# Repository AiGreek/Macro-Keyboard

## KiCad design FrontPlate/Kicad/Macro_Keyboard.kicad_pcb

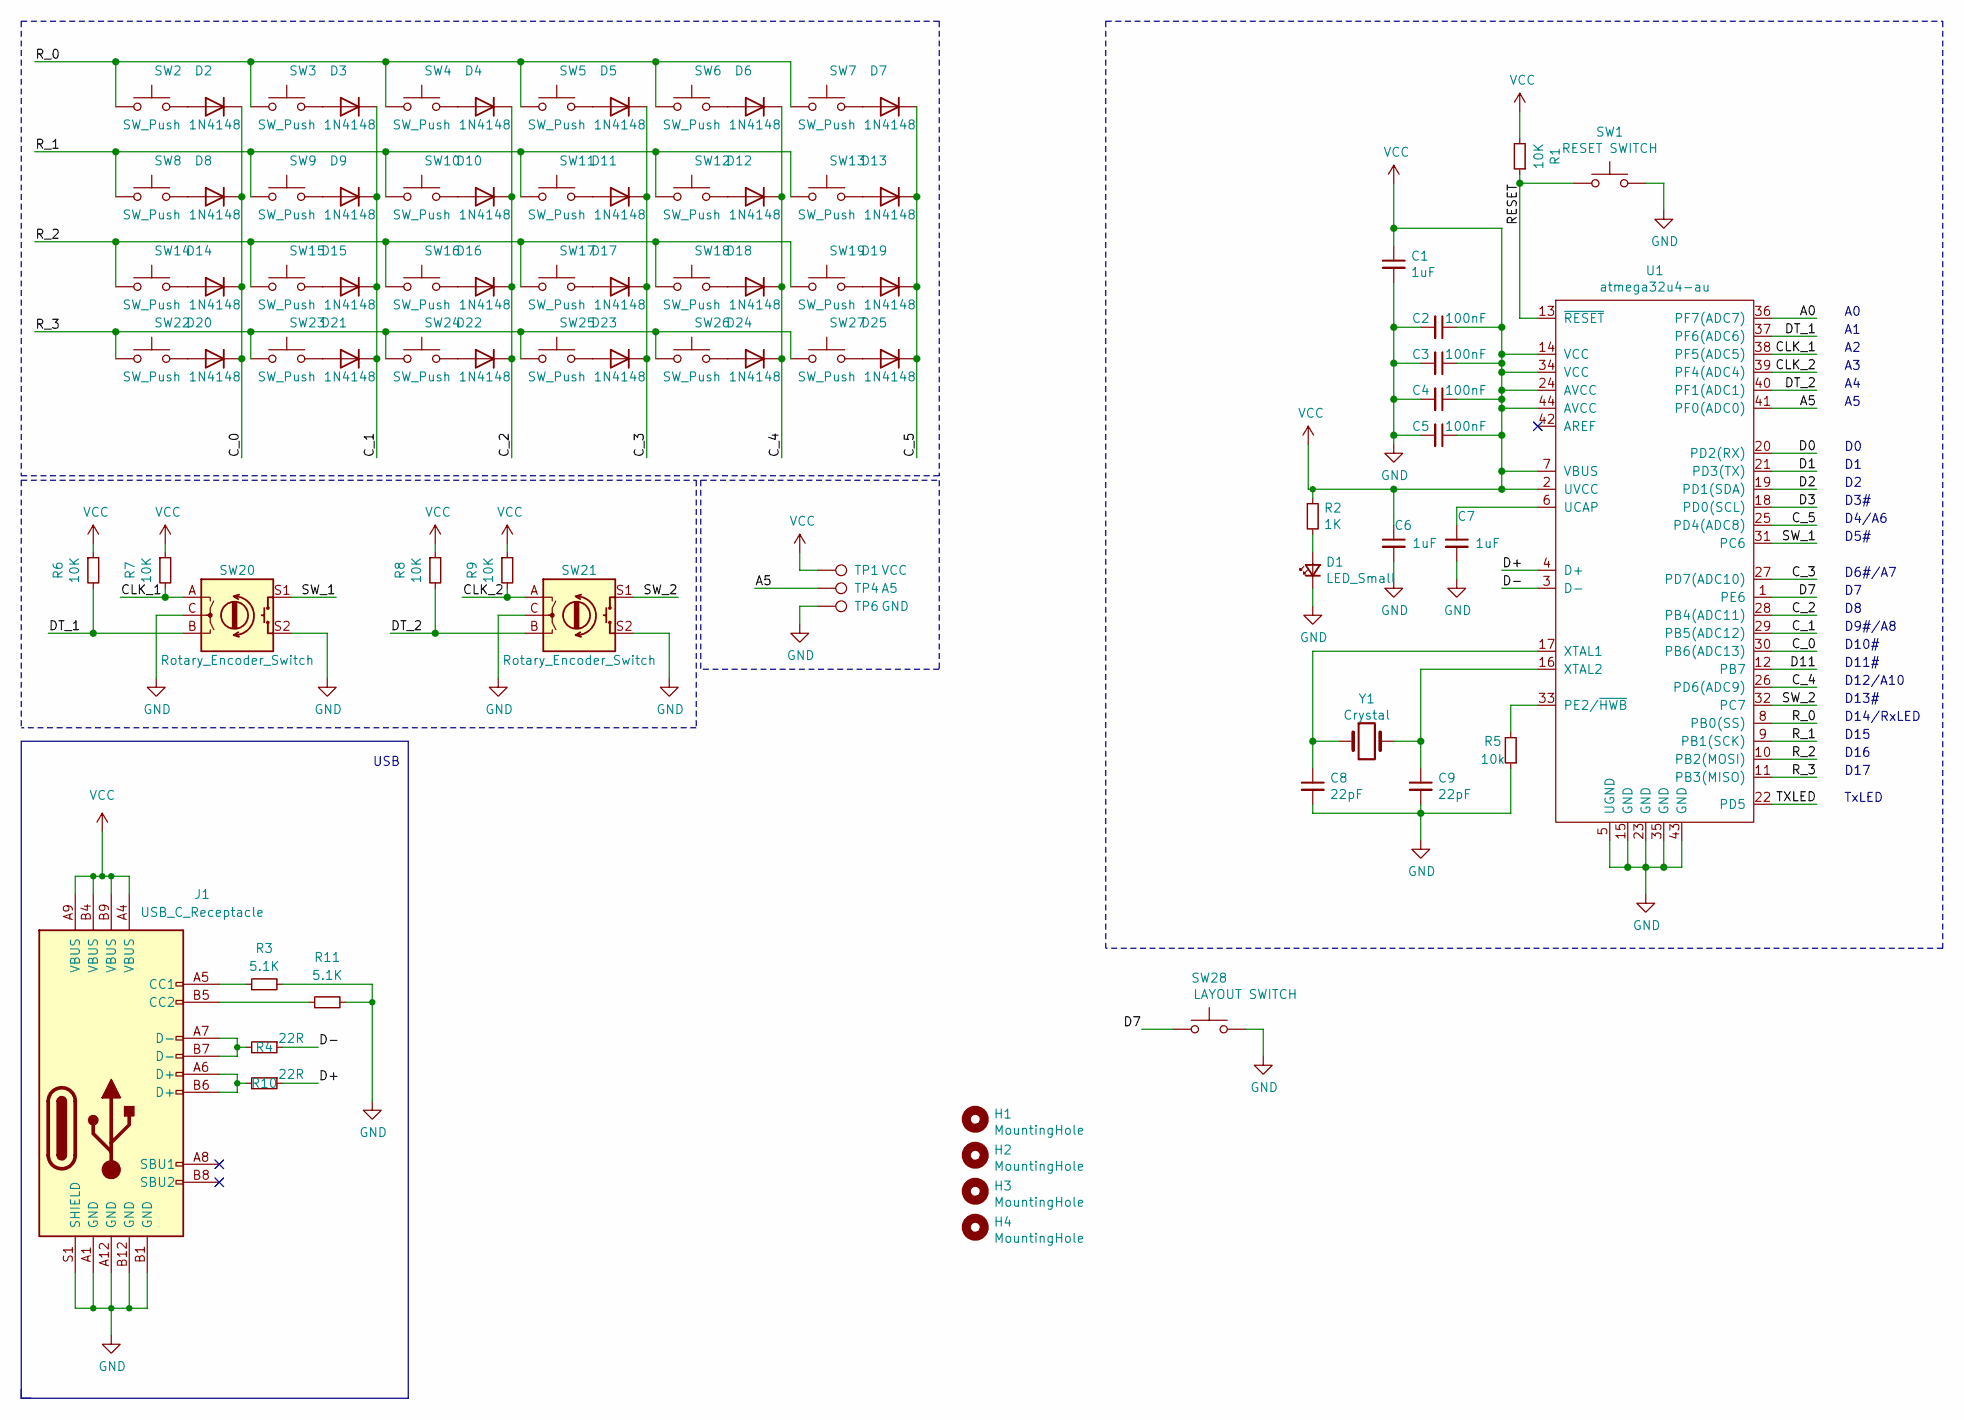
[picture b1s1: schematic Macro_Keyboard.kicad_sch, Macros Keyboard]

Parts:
C1, C6, C7: 1uF; C_0603_1608Metric_Pad1.08x0.95mm_HandSolder; LCSC C15849
C2, C3, C4, C5: 100nF; C_0603_1608Metric_Pad1.08x0.95mm_HandSolder; LCSC C83054
C8, C9: 22pF; C_0603_1608Metric_Pad1.08x0.95mm_HandSolder; LCSC C1653
D1: LED_Small; LED_0603_1608Metric_Pad1.05x0.95mm_HandSolder; LCSC C72044
D2, D3, D4, D5, D6, D7, D8, D9, D10, D11, D12, D13, D14, D15, D16, D17, D18, D19, D20, D21, D22, D23, D24, D25: 1N4148; D_SOD-123; LCSC C81598
H1, H2, H3, H4: MountingHole; MountingHole_3.2mm_M3_DIN965_Pad
J1: USB_C_Receptacle; USB_C_Receptacle_JAE_DX07S016JA1R1500; LCSC C668624
R1, R6, R7, R8, R9: 10K; R_0603_1608Metric_Pad0.98x0.95mm_HandSolder; LCSC C25804
R2: 1K; R_0603_1608Metric_Pad0.98x0.95mm_HandSolder; LCSC C4177
R3, R11: 5.1K; R_0603_1608Metric_Pad0.98x0.95mm_HandSolder; LCSC C26000
R4, R10: 22R; R_0603_1608Metric_Pad0.98x0.95mm_HandSolder; LCSC C23345
R5: 10k; R_0603_1608Metric_Pad0.98x0.95mm_HandSolder; LCSC C25804
SW1: RESET SWITCH; SW_SPST_SKQG_WithStem; LCSC C92584
SW2, SW3, SW4, SW5, SW6, SW7, SW8, SW9, SW10, SW11, SW12, SW13, SW14, SW15, SW16, SW17, SW18, SW19, SW22, SW23, SW24, SW25, SW26, SW27: SW_Push; SW_Cherry_MX_1.00u_PCB
SW20, SW21: Rotary_Encoder_Switch; RotaryEncoder_Alps_EC11E-Switch_Vertical_H20mm
SW28: LAYOUT SWITCH; SW_Tactile_SPST_Angled_PTS645Vx83-2LFS; LCSC C273481
TP1: VCC; PinHeader_1x01_P2.54mm_Vertical
TP4: A5; PinHeader_1x01_P2.54mm_Vertical
TP6: GND; PinHeader_1x01_P2.54mm_Vertical
U1: atmega32u4-au; TQFP-44_10x10mm_P0.8mm; LCSC C44854
Y1: Crystal; Crystal_SMD_3225-4Pin_3.2x2.5mm

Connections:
/A0: U1.36 (PF7(ADC7))
/A5: TP4.1, U1.41 (PF0(ADC0))
/CLK_1: R7.2, SW20.A, U1.38 (PF5(ADC5))
/CLK_2: R9.2, SW21.A, U1.39 (PF4(ADC4))
/C_0: D2.1 (K), D8.1 (K), D14.1 (K), D20.1 (K), U1.30 (PB6(ADC13))
/C_1: D3.1 (K), D9.1 (K), D15.1 (K), D21.1 (K), U1.29 (PB5(ADC12))
/C_2: D4.1 (K), D10.1 (K), D16.1 (K), D22.1 (K), U1.28 (PB4(ADC11))
/C_3: D5.1 (K), D11.1 (K), D17.1 (K), D23.1 (K), U1.27 (PD7(ADC10))
/C_4: D6.1 (K), D12.1 (K), D18.1 (K), D24.1 (K), U1.26 (PD6(ADC9))
/C_5: D7.1 (K), D13.1 (K), D19.1 (K), D25.1 (K), U1.25 (PD4(ADC8))
/D0: U1.20 (PD2(RX))
/D1: U1.21 (PD3(TX))
/D2: U1.19 (PD1(SDA))
/D3: U1.18 (PD0(SCL))
/D7: SW28.1, U1.1 (PE6)
/D11: U1.12 (PB7)
/D+: R10.1, U1.4 (D+)
/D-: R4.1, U1.3 (D-)
/DT_1: R6.2, SW20.B, U1.37 (PF6(ADC6))
/DT_2: R8.2, SW21.B, U1.40 (PF1(ADC1))
/RESET: R1.1, SW1.1, U1.13 (~RESET)
/R_0: SW2.1, SW3.1, SW4.1, SW5.1, SW6.1, SW7.1, U1.8 (PB0(SS))
/R_1: SW8.1, SW9.1, SW10.1, SW11.1, SW12.1, SW13.1, U1.9 (PB1(SCK))
/R_2: SW14.1, SW15.1, SW16.1, SW17.1, SW18.1, SW19.1, U1.10 (PB2(MOSI))
/R_3: SW22.1, SW23.1, SW24.1, SW25.1, SW26.1, SW27.1, U1.11 (PB3(MISO))
/SW_1: SW20.S1, U1.31 (PC6)
/SW_2: SW21.S1, U1.32 (PC7)
/TXLED: U1.22 (PD5)
GND: C1.2, C2.2, C3.2, C4.2, C5.2, C6.2, C7.2, C8.2, C9.2, D1.1 (K), J1.A1 (GND), J1.A12 (GND), J1.B1 (GND), J1.B12 (GND), J1.S1 (SHIELD), R3.2, R5.1, R11.2, SW1.2, SW20.C, SW20.S2, SW21.C, SW21.S2, SW28.2, TP6.1, U1.5 (UGND), U1.15 (GND), U1.23 (GND), U1.35 (GND), U1.43 (GND)
unnamed: D1.2 (A), R2.2
unnamed: D2.2 (A), SW2.2
unnamed: D3.2 (A), SW3.2
unnamed: D4.2 (A), SW4.2
unnamed: D5.2 (A), SW5.2
unnamed: D6.2 (A), SW6.2
unnamed: D7.2 (A), SW7.2
unnamed: D8.2 (A), SW8.2
unnamed: D9.2 (A), SW9.2
unnamed: D10.2 (A), SW10.2
unnamed: D11.2 (A), SW11.2
unnamed: D12.2 (A), SW12.2
unnamed: D13.2 (A), SW13.2
unnamed: D14.2 (A), SW14.2
unnamed: D15.2 (A), SW15.2
unnamed: D16.2 (A), SW16.2
unnamed: D17.2 (A), SW17.2
unnamed: D18.2 (A), SW18.2
unnamed: D19.2 (A), SW19.2
unnamed: D20.2 (A), SW22.2
unnamed: D21.2 (A), SW23.2
unnamed: D22.2 (A), SW24.2
unnamed: D23.2 (A), SW25.2
unnamed: D24.2 (A), SW26.2
unnamed: D25.2 (A), SW27.2
unnamed: J1.A5 (CC1), R3.1
unnamed: J1.B5 (CC2), R11.1
unnamed: J1.A6 (D+), J1.B6 (D+), R10.2
unnamed: J1.A7 (D-), J1.B7 (D-), R4.2
unnamed: R5.2, U1.33 (PE2/~HWB)
unnamed: C7.1, U1.6 (UCAP)
unnamed: C8.1, U1.17 (XTAL1), Y1.1
unnamed: C9.1, U1.16 (XTAL2), Y1.2
VCC: C1.1, C2.1, C3.1, C4.1, C5.1, C6.1, J1.A4 (VBUS), J1.A9 (VBUS), J1.B4 (VBUS), J1.B9 (VBUS), R1.2, R2.1, R6.1, R7.1, R8.1, R9.1, TP1.1, U1.2 (UVCC), U1.7 (VBUS), U1.14 (VCC), U1.24 (AVCC), U1.34 (VCC), U1.44 (AVCC)

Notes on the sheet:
D10#
D15
D16
D4/A6
D9#/A8
USB
D11#
D14/RxLED
D13#
D12/A10
D17
D6#/A7
D5#
TxLED
D3#

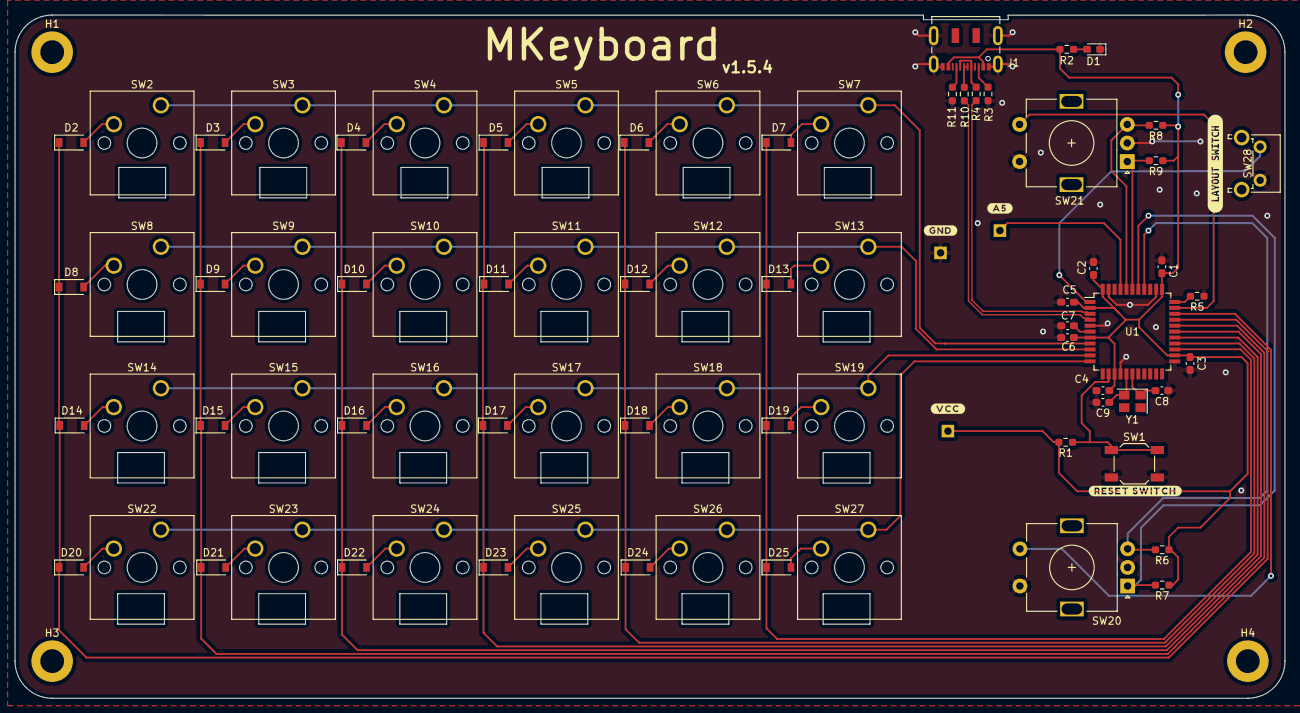
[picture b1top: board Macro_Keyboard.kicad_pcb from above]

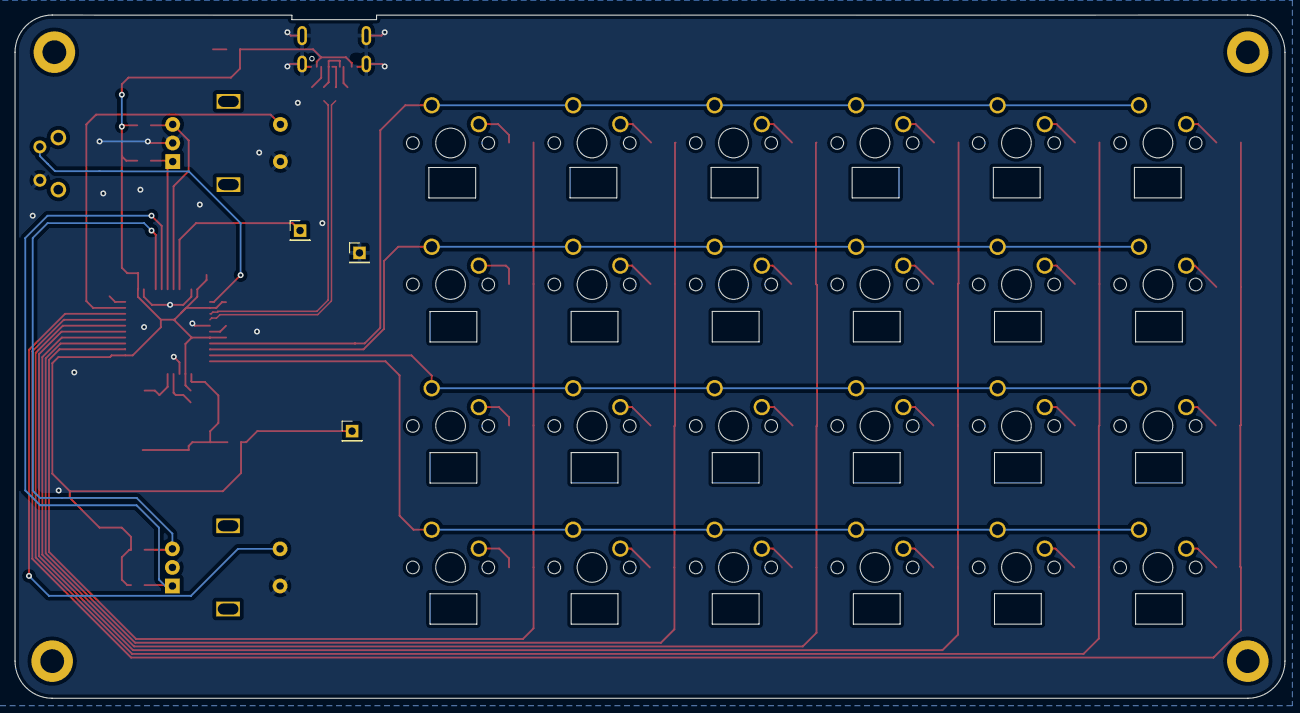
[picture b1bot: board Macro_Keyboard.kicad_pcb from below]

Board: 2 copper layers, 171.0 x 92.0 mm, 84 parts (3 on the bottom side), 56 nets.

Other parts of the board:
kibuzzard-61CABCC7: G***; kibuzzard-61CABCC7

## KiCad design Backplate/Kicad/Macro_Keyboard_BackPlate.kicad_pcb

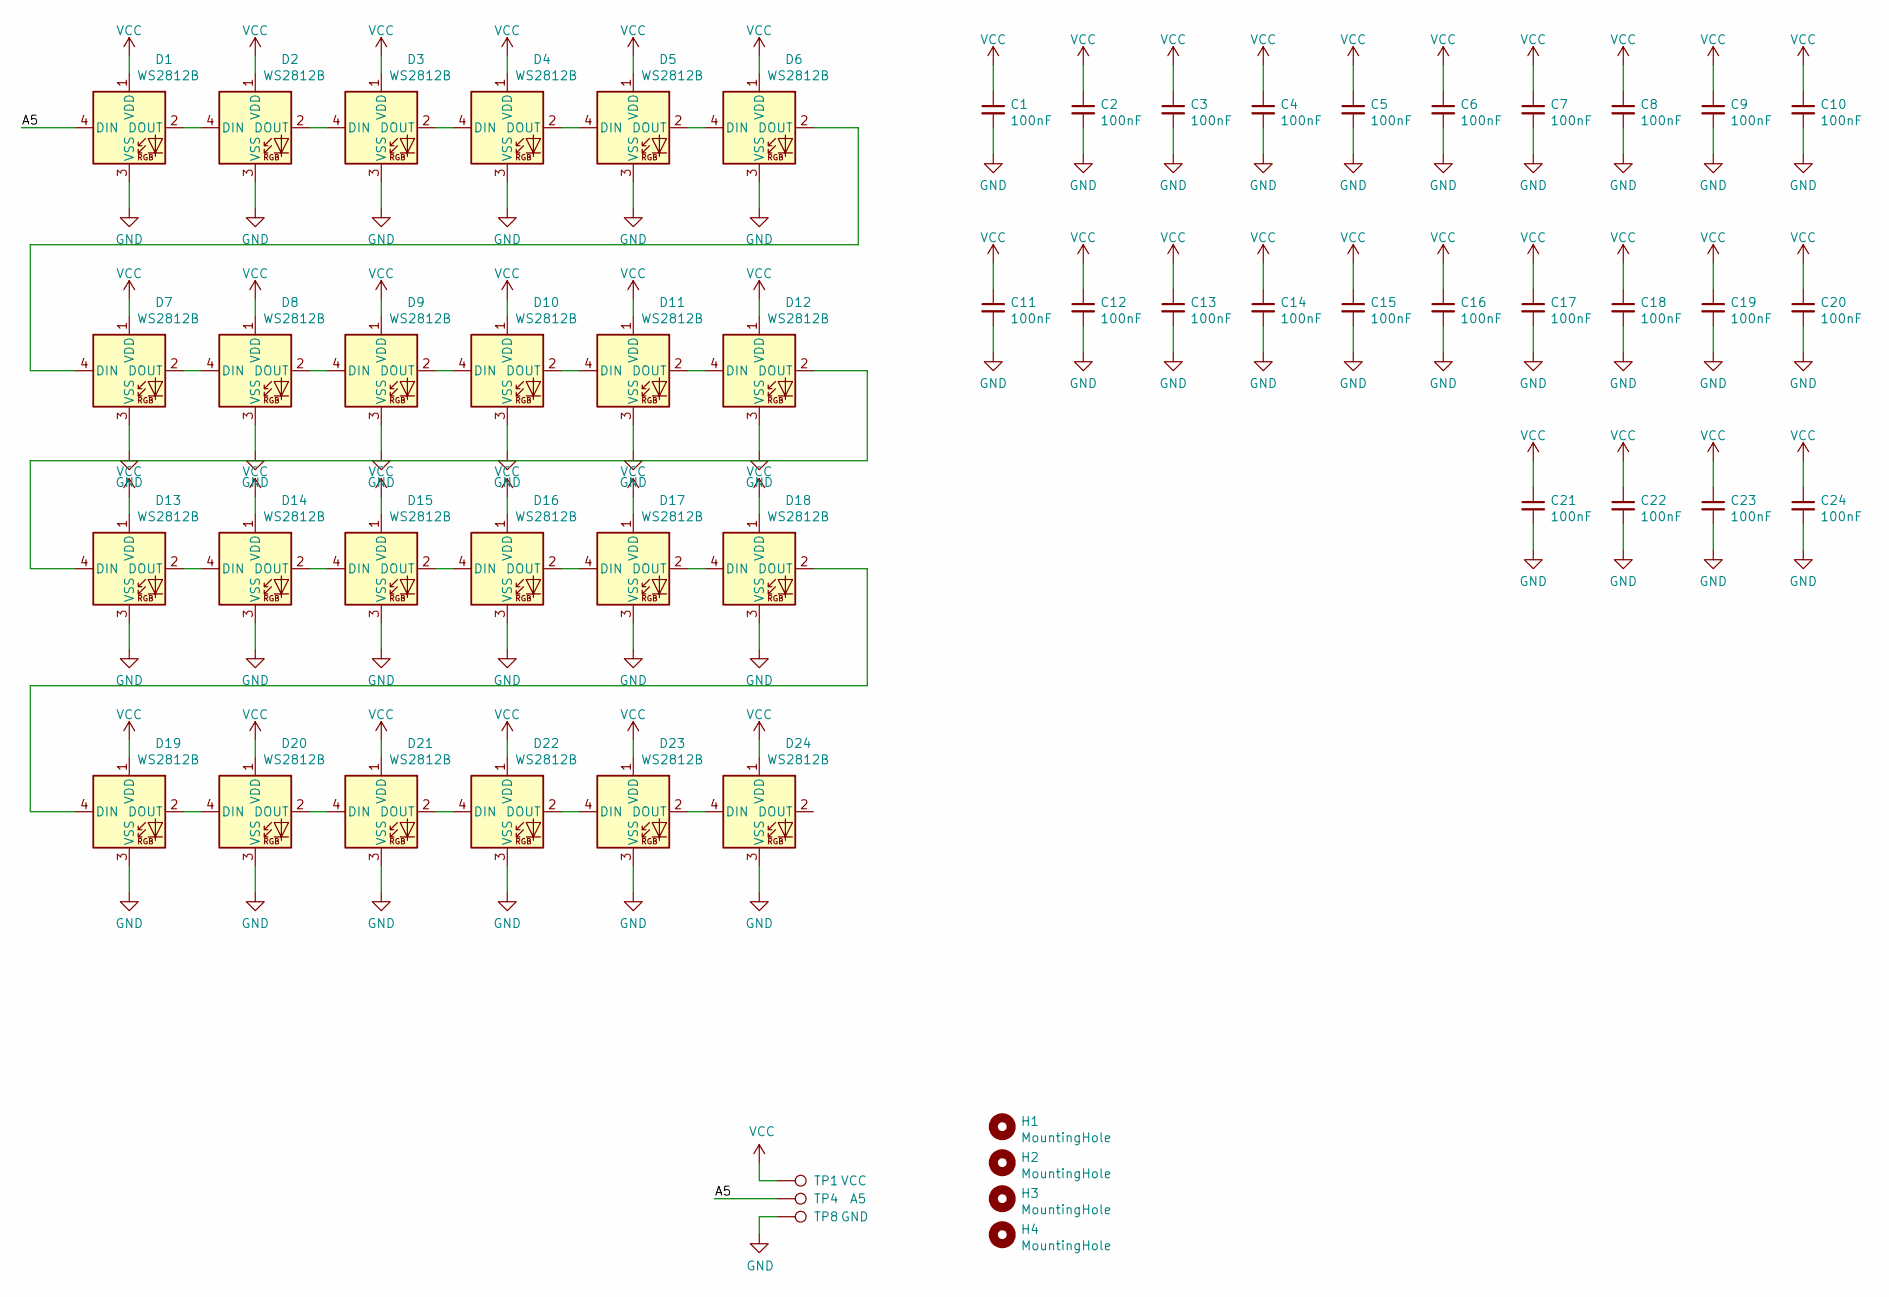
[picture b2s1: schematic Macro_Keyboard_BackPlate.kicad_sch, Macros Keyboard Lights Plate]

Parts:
C1, C2, C3, C4, C5, C6, C7, C8, C9, C10, C11, C12, C13, C14, C15, C16, C17, C18, C19, C20, C21, C22, C23, C24: 100nF; C_0603_1608Metric; LCSC C14663
D1, D2, D3, D4, D5, D6, D7, D8, D9, D10, D11, D12, D13, D14, D15, D16, D17, D18, D19, D20, D21, D22, D23, D24: WS2812B; LED_WS2812B_PLCC4_5.0x5.0mm_P3.2mm; LCSC C114586
H1, H2, H3, H4: MountingHole; MountingHole_3.2mm_M3_DIN965_Pad
TP1: VCC; PinHeader_1x01_P2.54mm_Vertical
TP4: A5; PinHeader_1x01_P2.54mm_Vertical
TP8: GND; PinHeader_1x01_P2.54mm_Vertical

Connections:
/A5: D1.4 (DIN), TP4.1
GND: C1.2, C2.2, C3.2, C4.2, C5.2, C6.2, C7.2, C8.2, C9.2, C10.2, C11.2, C12.2, C13.2, C14.2, C15.2, C16.2, C17.2, C18.2, C19.2, C20.2, C21.2, C22.2, C23.2, C24.2, D1.3 (VSS), D2.3 (VSS), D3.3 (VSS), D4.3 (VSS), D5.3 (VSS), D6.3 (VSS), D7.3 (VSS), D8.3 (VSS), D9.3 (VSS), D10.3 (VSS), D11.3 (VSS), D12.3 (VSS), D13.3 (VSS), D14.3 (VSS), D15.3 (VSS), D16.3 (VSS), D17.3 (VSS), D18.3 (VSS), D19.3 (VSS), D20.3 (VSS), D21.3 (VSS), D22.3 (VSS), D23.3 (VSS), D24.3 (VSS), TP8.1
unnamed: D1.2 (DOUT), D2.4 (DIN)
unnamed: D2.2 (DOUT), D3.4 (DIN)
unnamed: D3.2 (DOUT), D4.4 (DIN)
unnamed: D4.2 (DOUT), D5.4 (DIN)
unnamed: D5.2 (DOUT), D6.4 (DIN)
unnamed: D6.2 (DOUT), D7.4 (DIN)
unnamed: D7.2 (DOUT), D8.4 (DIN)
unnamed: D8.2 (DOUT), D9.4 (DIN)
unnamed: D10.2 (DOUT), D11.4 (DIN)
unnamed: D9.2 (DOUT), D10.4 (DIN)
unnamed: D11.2 (DOUT), D12.4 (DIN)
unnamed: D12.2 (DOUT), D13.4 (DIN)
unnamed: D13.2 (DOUT), D14.4 (DIN)
unnamed: D14.2 (DOUT), D15.4 (DIN)
unnamed: D15.2 (DOUT), D16.4 (DIN)
unnamed: D16.2 (DOUT), D17.4 (DIN)
unnamed: D17.2 (DOUT), D18.4 (DIN)
unnamed: D18.2 (DOUT), D19.4 (DIN)
unnamed: D19.2 (DOUT), D20.4 (DIN)
unnamed: D20.2 (DOUT), D21.4 (DIN)
unnamed: D21.2 (DOUT), D22.4 (DIN)
unnamed: D22.2 (DOUT), D23.4 (DIN)
unnamed: D23.2 (DOUT), D24.4 (DIN)
VCC: C1.1, C2.1, C3.1, C4.1, C5.1, C6.1, C7.1, C8.1, C9.1, C10.1, C11.1, C12.1, C13.1, C14.1, C15.1, C16.1, C17.1, C18.1, C19.1, C20.1, C21.1, C22.1, C23.1, C24.1, D1.1 (VDD), D2.1 (VDD), D3.1 (VDD), D4.1 (VDD), D5.1 (VDD), D6.1 (VDD), D7.1 (VDD), D8.1 (VDD), D9.1 (VDD), D10.1 (VDD), D11.1 (VDD), D12.1 (VDD), D13.1 (VDD), D14.1 (VDD), D15.1 (VDD), D16.1 (VDD), D17.1 (VDD), D18.1 (VDD), D19.1 (VDD), D20.1 (VDD), D21.1 (VDD), D22.1 (VDD), D23.1 (VDD), D24.1 (VDD), TP1.1

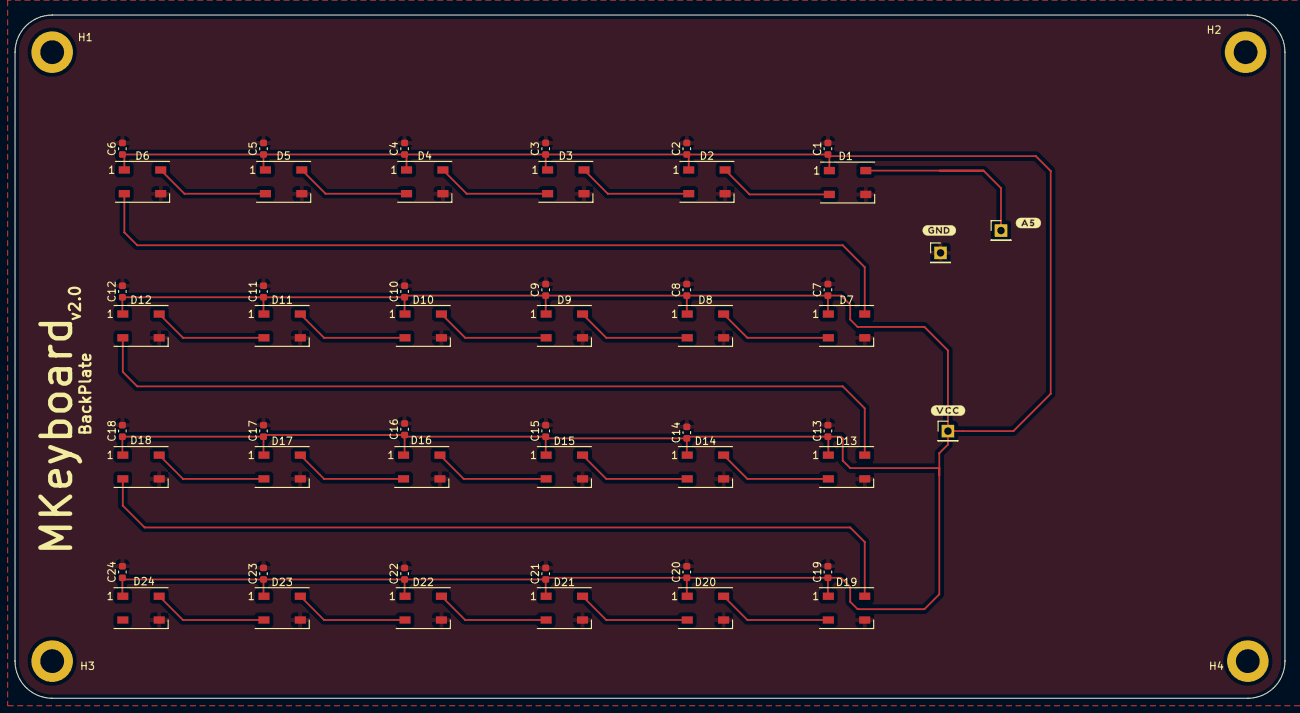
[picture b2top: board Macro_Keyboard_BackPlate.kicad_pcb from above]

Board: 2 copper layers, 171.0 x 92.0 mm, 55 parts (0 on the bottom side), 26 nets.
